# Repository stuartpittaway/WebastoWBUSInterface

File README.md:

# WebastoWBUSInterface

Hardware circuit and diagram for interfacing to the Webasto WBUS interface from a PC/Arduino

This small circuit allows you to connect a 5 volt device with a serial port to a Webasto Heater which communicates in the WBUS protocol.

The circuit expects you to connect a FT232R USB Serial to TTL interface, or a micro controller such as the Arduino.

Its a http://fritzing.org/home/ circuit/file so you can make a PCB from it if you want (not tested!).

It uses hardly any parts, costs less than £1 (GBP) to make.

Amount 	Part Type 	Properties
1 	Generic female header - 3 pins 	row single; hole size 1.0mm,0.508mm; pin spacing 0.1in (2.54mm); pins 3; form ♀ (female); package THT
3 	NPN-Transistor 	variant variant 2; type NPN (EBC); package TO92 [THT]; part # BC548 NPN
1 	Generic female header - 6 pins 	row single; hole size 1.0mm,0.508mm; pin spacing 0.1in (2.54mm); pins 6; form ♀ (female); package THT; part # FTDI BASIC
1 	Yellow (595nm) LED 	color Yellow (595nm); package 3 mm [THT]; 
1 	PNP-Transistor 	type PNP (CBE); package TO92 [THT]; part # BC557 PNP
4 	10kΩ Resistor 	bands 4; tolerance ±5%; pin spacing 400 mil; resistance 10kΩ; package THT
3 	1kΩ Resistor 	bands 4; tolerance ±5%; pin spacing 400 mil; resistance 1kΩ; package THT

Have fun!

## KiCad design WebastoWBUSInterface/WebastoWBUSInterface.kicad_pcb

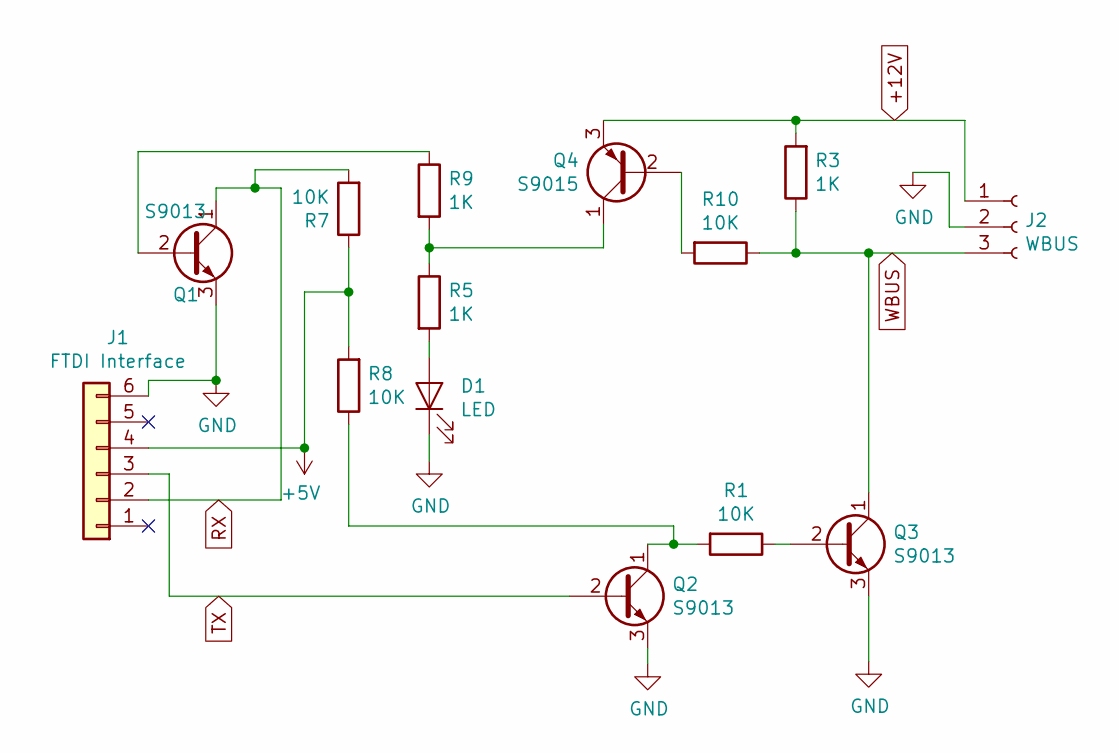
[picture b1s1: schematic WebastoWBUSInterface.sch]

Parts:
D1: LED; LED_0603_HandSoldering; JLCPCBPartNumber C72043
J1: FTDI Interface; Socket_Strip_Angled_1x06_Pitch2.54mm
J2: WBUS; TerminalBlock_bornier-3_P5.08mm
Q1, Q2, Q3: S9013; SOT-23; Part S9013; JLCPCBPartNumber C6749
Q4: S9015; SOT-23; Part S9015; JLCPCBPartNumber C2149
R1, R7, R8, R10: 10K; R_0805_HandSoldering; Part 0805W8F1002T5E; JLCPCBPartNumber C17414
R3, R5, R9: 1K; R_0805_HandSoldering; Part 0805W8F1001T5E; JLCPCBPartNumber C17513

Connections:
+5V: J1.4, R7.1, R8.2
+12V: J2.1, Q4.3 (E), R3.2
GND: D1.1 (K), J1.6, J2.2, Q1.3 (E), Q2.3 (E), Q3.3 (E)
unnamed: D1.2 (A), R5.2
unnamed: Q1.2 (B), R9.1
unnamed: Q2.1 (C), R1.2, R8.1
unnamed: Q3.2 (B), R1.1
unnamed: Q4.1 (C), R5.1, R9.2
unnamed: Q4.2 (B), R10.2
RX: J1.2, Q1.1 (C), R7.2
TX: J1.3, Q2.2 (B)
WBUS: J2.3, Q3.1 (C), R3.1, R10.1

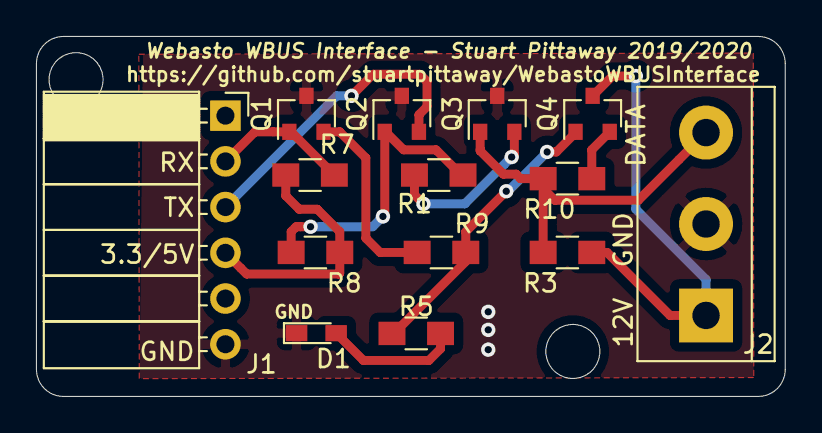
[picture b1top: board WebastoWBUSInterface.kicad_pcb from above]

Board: 2 copper layers, 41.6 x 20.0 mm, 14 parts (0 on the bottom side), 12 nets.

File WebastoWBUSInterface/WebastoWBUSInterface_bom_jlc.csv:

"Comment","Designator","Footprint","LCSC Part #"
"LED","D1","LED_0603_HandSoldering","C72043"
"S9013","Q3,Q2,Q1","SOT-23","C6749"
"S9015","Q4","SOT-23","C2149"
"10K","R1,R8,R10,R7","R_0805_HandSoldering","C17414"
"1K","R3,R5,R9","R_0805_HandSoldering","C17513"

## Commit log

2015-03-16 Updated with B.O.M
2015-03-16 Updated PCB
2019-11-24 Recreated design using KICAD for PCB production
2019-12-29 Larger resistor hole sizes
2019-12-29 Remove backup files
2019-12-29 JLCPCB SMD board for full assembly
